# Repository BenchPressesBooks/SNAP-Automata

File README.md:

# SNAP-Automata

## Table of contents
1. [Introduction](#introduction)
2. [Automation](#automation)
3. [Controller Configuration](#controller-configuration)
4. [Home Assistant Additions](#home-assistant-additions)

## Introduction
I have always wanted a home automation system that is affordable and completely home-brew so I began on this journey in August 2017. This system was designed with cost minimization, energy efficiency, convenience, and ease of use for me and visitors in mind.

More detail is provided below, but a majority of this system is driven using WeMos D1 Pro ESP8266 devices, Arduino Uno devices, HomeAssistant and Mosquitto. This setup is completely free with the exception of the hardware. I will add details outlining the products I used in a future revision of this readme.

### Architecture

Server Infrastructure:
- Centos7 (minimal install)
- Provides the only access in or out of the IoT VLAN
- Remote syslogging to Splunk for diagnostics and historical device usage
- NTP from core switch
	
Above server virtualized using ESXI (Minimal specs due to nature of device)
- i7 Processor
- Gigabit Ethernet connection
- 2GB RAM
- 15GB disk space

Network Infrastructure:
- IoT VLAN isolates all devices, available via wireless and wired networks
- Firewall configured to block all inbound, outbound, and cross-device communication 
- Only communication allowed directly through MQTT broker
	
Software Infrastructure:
- MQTT Dash for Android
- IoT endpoints using MQTT library for control and 
- HomeAssistant as automation and interface
- Mosquitto as MQTT broker	

## Automation

Exterior Rules:
- Front path lights turn on before leaving for work and off at sunrise but only on weekdays
- Front path lights turn on again at sundown and turn off at a set time
- All other permanent exterior devices turn on only when manually triggered
- All exterior devices turn off at midnight regardless of how they were triggered (unless automation override is enabled)
- Christmas lights (when installed) come on 30 min before sunset and run until 23:00

Interior Rules:
- Living room side lamp follows schedule of front path lights but turns on 30 minutes early in the morning and off 30 minutes late at night
- Display cases are triggered manually or by party mode. I will eventually turn these into presence devices
- Cactus and Succulent grow lights turn on 1 hour after sunrise, turn off 1 hour before sunset to supplement sunlight (during winter)

## Controller Configuration
### Home Assistant
The minimal install of Centos doesn't come with the packages we need to run HomeAssistant, so our first step will be getting those installed.

```
sudo yum install centos-release-scl
sudo yum install rh-python35
```

Set up a system user and group for home assistant to use. I will configure it to run under the user and group 'homeassistant'. I HIGHLY recommend not running software as root for security and granularity reasons.

```
sudo useradd --system homeassistant
sudo groupadd homeassistant
sudo usermod -a -G homeassistant
```

Next let’s create the install dir, then home directory

```
sudo mkdir /srv/homeassistant
sudo chown homeassistant:homeassistant /srv/homeassistant
sudo su -s /bin/bash homeassistant
```

Next enable the software collection installed above and verify the Python version

```
scl enable rh-python35 bash
python --version
```

It should return `Python 3.5.x`. I decided to install and use this in a virtual environment. You can decide what is best for you with some basic research.

```
virtualenv -p python3 /srv/homeassistant
source /srv/homeassistant/bin/activate
```

Your prompt should now include (homeassistant). Now we are ready to install HASS in our virtual environment.

```
pip3 install --upgrade homeassistant
```

Home assistant should now be installed. It can by using

```
sudo -u homeassistant -H /srv/homeassistant/bin/hass
```

In order to make Home Assistant run on boot, we need to create a service. Luckily this already exists! Just download the service file from my repo above, or run the following command:

```
sudo wget https://raw.githubusercontent.com/BenchPressesBooks/SNAP-Automata/master/services/home-assistant%40homeassistant.service -O /etc/systemd/system/home-assistant@homeassistant.service
```

To make the daemon aware of the new configuration, reload systemd

```
sudo systemctl --system daemon-reload
sudo systemctl enable home-assistant@homeassistant
sudo systemctl start home-assistant@homeassistant
```

Upgrading HASS is easy now, just type

```
sudo su -s /bin/bash homeassistant
source /srv/homeassistant/bin/activate
pip3 install --upgrade homeassistant
```

The main configuration file for HomeAssistant is at `/home/hass/.homeassistant/configuration.yaml`
The main logs file is at `/home/hass/.homeassistant/home-assistant.log`

### Mosquitto MQTT Messaging Broker
To install Mosquitto you will have to add another package to centos that is not included in the minimum install

```
sudo yum -y install epel-release
```

Now you can install the broker using yum. This is preferred to a manual install as `yum update` will keep this package at the latest version.

```
sudo yum install mosquitto
```

You will probably also want this to run at startup. Luckily the service daemon is already included with the package

```
sudo systemctl start mosquitto
sudo systemctl enable mosquitto
```

MQTT is a great protocol because it allows for ACL based security, which means you will need to create users

```
sudo touch /etc/mosquitto/conf.d/pwfile
sudo mosquitto_passwd /etc/mosquitto/conf.d/pwfile <mosquitto_username> <mosquitto_password>
```

To configure publishing and subscribing, create an `aclfile`

```
sudo touch /etc/mosquitto/conf.d/aclfile
```

NOTE: Using the batch mode above for mosquitto_passwd will make the password available in your bashhistory file. Heed caution when using this method.

I used `ha` as my main user for HomeAssistant to communicate with Mosquitto. This will be visible in my ACLFILE in the repo above.
To link Home Assistant with the Mosquitto broker, `configuration.yaml` will need to have the lines below added

```yaml
mqtt:
  broker: 'localhost' #127.0.0.1
  port: 1883
  client_id: 'ha'
  username: '<mosquitto_username>'
  password: '<mosquitto_password>'
```

The configuration file for Mosquitto is located at `/etc/mosquitto/conf.d/mosquitto.conf`
The log file is located at `/var/log/mosquitto/mosquitto.log`

## Home Assistant Additions
To start with this project, I decided to include DarkSky as a weather monitor. You will have to register at their website to get an API key. Once you receive that the sensor can be added to the sensors.yaml file. You will find mine in the configuration directory of the repo. I may eventually add more sensors to this project, but for the time being I am focusing on hardware design and cost-cutting.

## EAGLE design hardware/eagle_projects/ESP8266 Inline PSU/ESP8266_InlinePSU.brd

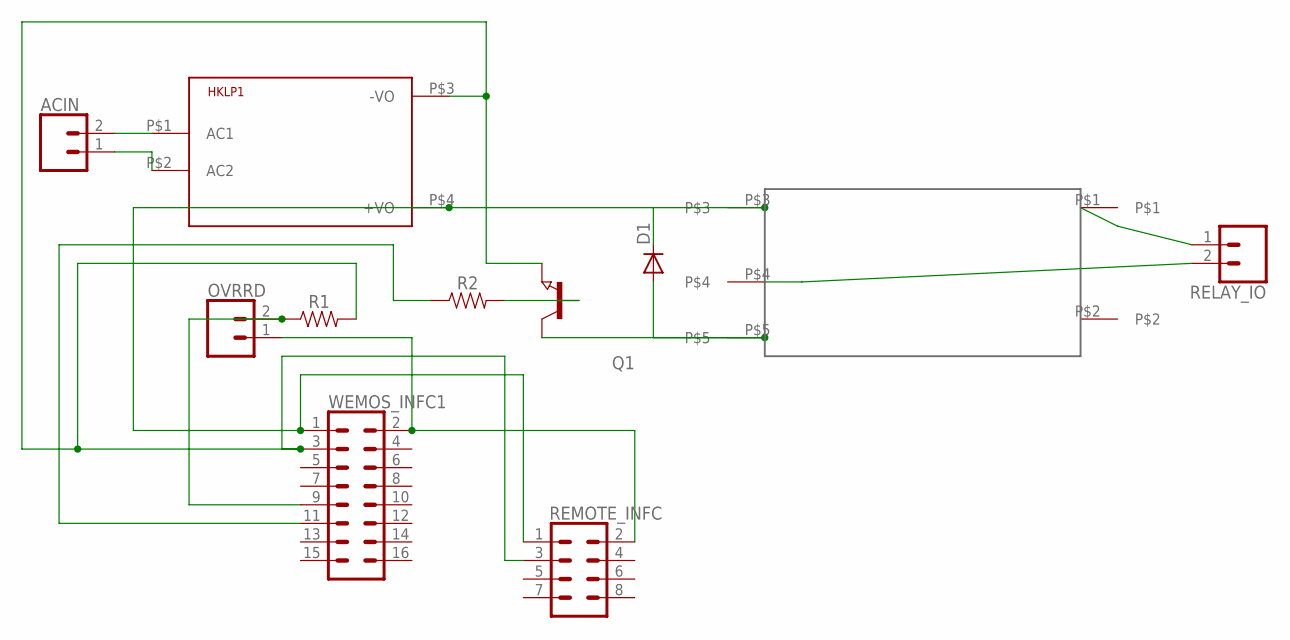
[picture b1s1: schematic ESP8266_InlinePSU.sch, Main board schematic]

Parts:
ACIN: CONN_025MM; SCREWTERMINAL-5MM-2
D1: 1N4148DO35-7; DO35-7
HKLP1: HKLPM01
OVRRD: CONN_02LOCK; 1X02_LOCK
Q1: NPN-TRANSISTOR_SOT23; SOT23
R1, R2: 0805
RELAY_IO: CONN_025MM; SCREWTERMINAL-5MM-2
REMOTE_INFC: CONN_04X2; 2X4
U$1: SRD-05VDC-SL-CTH; SRD-05VDC-SL-C
WEMOS_INFC1: CONN_08X2; 2X8

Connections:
unnamed: ACIN.2, HKLP1.P$1 (AC1)
unnamed: ACIN.1, HKLP1.P$2 (AC2)
unnamed: D1.C, HKLP1.P$4 (+VO), REMOTE_INFC.1, U$1.P$3, WEMOS_INFC1.1
unnamed: OVRRD.1, REMOTE_INFC.2, WEMOS_INFC1.2
unnamed: HKLP1.P$3 (-VO), Q1.2 (E), R1.2, REMOTE_INFC.3, WEMOS_INFC1.3
unnamed: RELAY_IO.1, U$1.P$1
unnamed: RELAY_IO.2, U$1.P$4
unnamed: D1.A, Q1.3 (C), U$1.P$5
unnamed: OVRRD.2, R1.1, WEMOS_INFC1.9
unnamed: Q1.1 (B), R2.2
unnamed: R2.1, WEMOS_INFC1.11

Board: 2 copper layers, 11 parts (0 on the bottom side), 11 nets, no tracks yet.

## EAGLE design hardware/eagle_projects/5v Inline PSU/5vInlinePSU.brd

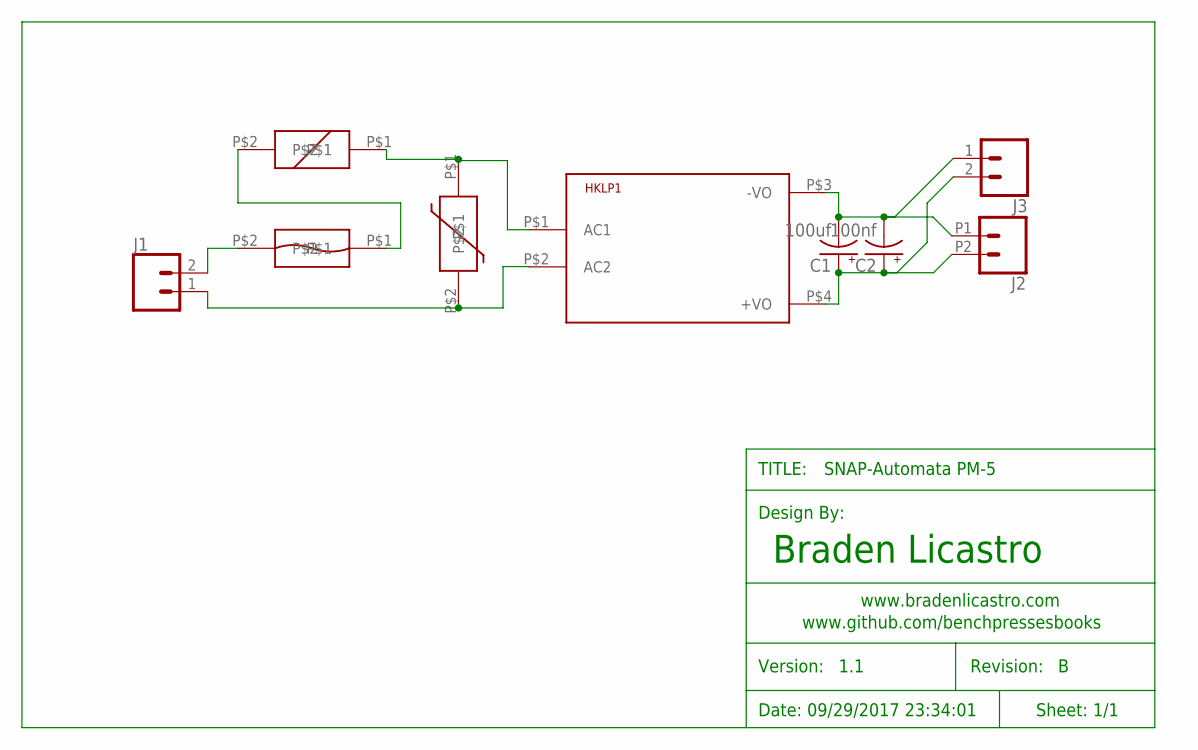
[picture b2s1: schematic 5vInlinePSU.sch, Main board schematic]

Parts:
C1: 100uf; E5-8,5
C2: 100nf; E2,5-6
HKLP1: HKLPM01
J1: CONN_025MM; SCREWTERMINAL-5MM-2
J2: CONN_022.54MM_SCREWTERM; 1X02_2.54_SCREWTERM
J3: CONN_02; 1X02
SDF: GENERIC_FUSE_3.6X10MMTHROUGH-HOLE; GENERIC_FUSE_3.6X10MM
U$2: THERMAL_FUSE_SF70ETHROUGH-HOLE; THERMAL_FUSE_SF70E
U$3: VARISTOR_TVR-07241THROUGH-HOLE; VARISTOR_TVR-07241

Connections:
unnamed: J1.2, SDF.P$2
unnamed: SDF.P$1, U$2.P$2
unnamed: HKLP1.P$1 (AC1), U$2.P$1, U$3.P$1
unnamed: HKLP1.P$2 (AC2), J1.1, U$3.P$2
unnamed: C1.-, C2.-, HKLP1.P$3 (-VO), J2.P1 (1), J3.1
unnamed: C1.+, C2.+, HKLP1.P$4 (+VO), J2.P2 (2), J3.2

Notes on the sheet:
Date: 09/29/2017 23:34:01
Sheet: 1/1
Design By:
Braden Licastro
TITLE:
SNAP-Automata PM-5
www.bradenlicastro.com
www.github.com/benchpressesbooks
Version:
Revision:
1.1

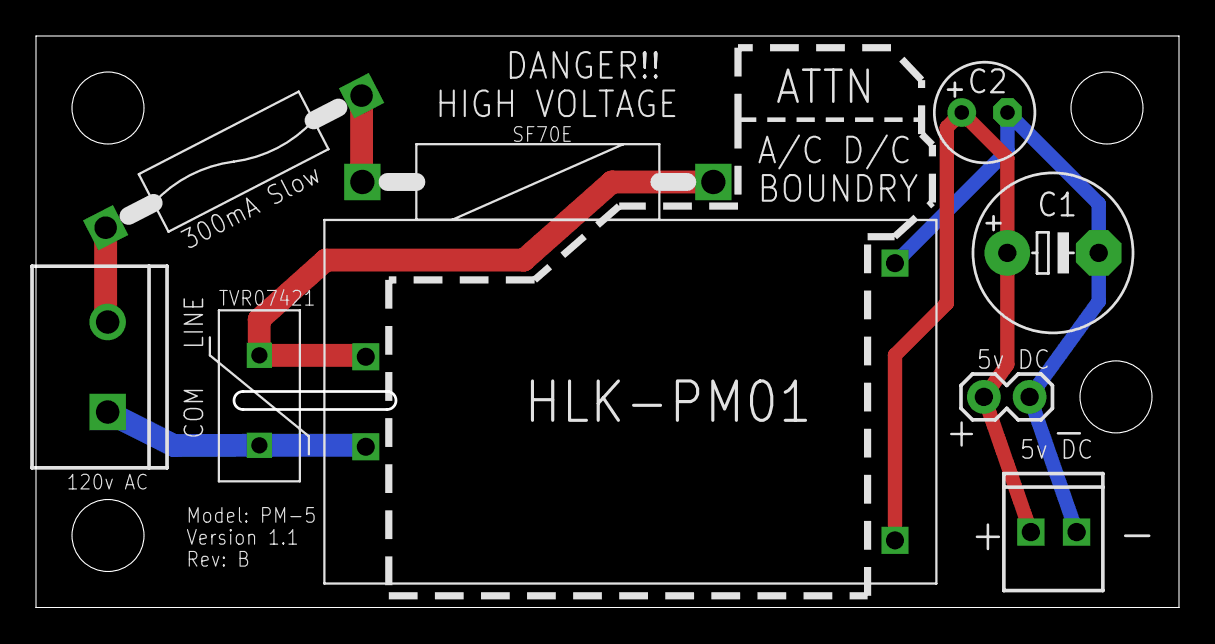
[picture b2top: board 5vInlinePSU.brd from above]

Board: 2 copper layers, 63.3 x 31.6 mm, 10 parts (0 on the bottom side), 6 nets.

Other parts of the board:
U$1: DANGER_SYMBOL

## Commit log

2017-09-21 Adding initial files and commiting readme change.
2017-09-21 Added homeassistant service file to readme
2017-09-21 Fixed wording in readme
2017-09-21 Fixed readme markdown
2017-09-29 Created PM-5 and added supporting resources. Also modified HASS and Mosquitto config and heirarchy.
2017-09-29 Updated Eagle custom library and gitignore.
2017-09-29 Error in rev heirarchy notation and added PDF of gerbers
2017-10-04 Adding two Wemos device sketches for first floor smart outlets.
2017-10-05 Added board config just in case this ever vanishes from the official source.
2017-10-05 Added sketch for getting mac address of new ESP8266 device.
2017-10-09 Added porch lighting code. Going to use this as base for all other devices after vetting.
2017-10-17 Removed exterior and rebranded to PathLights during code rewrite. Now accepts three button overrides and had improved formatting.
2017-10-17 Fixed comment formatting that was inconsistent.
2017-10-17 Rewrote large portion of ESP8266 device code to allow bypass and OTA code publishing. Also redacted device names on other sketches, though unimportant.
2017-10-25 Beginning build process for wireless inline PSU and modifications of PSU
2017-10-25 Added debounce for path light buttons and eliminated ALL delays to improve performance of device.
2017-10-25 Redesigned detection moving away from interrupt, fixed several nasty logic errors, added in switch debouncing, and started to work for automated recovery of errors and automated HTTP OTA publishing.
2017-11-10 Have a working model of the centralized server side OTA update system.
2017-11-10 Migrated code from dev device to display case.
2017-11-10 Made very minor comment formatting change for consistency.
2017-11-11 Fixed type error that was causing MQTT port to be incorrect.
2017-11-11 Didn't increment build number.
2017-11-11 Added server side OTA code and configurations with sample output logging.
2017-12-14 Completed more work on hardware design. Broke out sections of sensitive code, optimised existing code. Hacked new device for use and built new firmware. Updated test firmware for deployment on multip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
2017-12-15 Turned off debugging, edited formatting, and fixes MQTT topic issue.
2018-01-09 Massive changes to automation configuration and supporting systems
2018-01-20 Added a ton of new sketches and made changes to a few others.
2018-08-10 Made TONS of changes over last few months
2018-08-10 Purges a large number of old files in cleanup

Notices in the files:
hardware/eagle_projects/5v Inline PSU/5vInlinePSU.brd:
(c) 2017 Braden Licastro
parts and their libraries:
SparkFun-Connectors: Licensing: Creative Commons ShareAlike 4.0 International - https://creativecommons.org/licenses/by-sa/4.0
